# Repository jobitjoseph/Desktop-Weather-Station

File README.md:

# [Desktop-Weather-Station](https://circuitdigest.com/microcontroller-projects/)

---
<p>
  In today’s fast-paced world, many of us spend long hours indoors—whether working from home, studying, or just managing our daily routines. Natural cues like changing skies, outdoor temperatures, or the feel of humidity are often lost behind four walls and closed windows. This can make it difficult to stay aware of what’s happening outside, especially when our focus is tied to digital devices. Having a dedicated, always-visible weather display on your desk adds a subtle but meaningful connection to the outside world. It’s a small touch that can help with planning your day, knowing when to grab a jacket before stepping out, or simply enjoying the gentle reminder that time and weather continue to change beyond the screen.
</p>

<p>This project offers a practical way to build a clean and minimal weather station using an ESP32 microcontroller and an E-Ink display. The use of E-Ink ensures that the display remains readable even without constant power, making it a perfect fit for battery-powered desktop use. Once connected to Wi-Fi, the station fetches real-time weather data such as temperature, humidity, and current conditions using the OpenWeatherMap API. It also monitors indoor temperature and humidity with the help of a built-in sensor and adds to the data displayed on the screen. The device automatically updates itself at fixed intervals and enters deep sleep to conserve energy. Once assembled, it becomes a quiet and elegant companion on your desk—keeping you informed, without the distractions of a smartphone or computer screen.</p>

The firmware part of this project builds upon the excellent work of [David Bird](https://github.com/G6EJD/ESP32-e-Paper-Weather-Display). The code has been adapted from his original implementation.

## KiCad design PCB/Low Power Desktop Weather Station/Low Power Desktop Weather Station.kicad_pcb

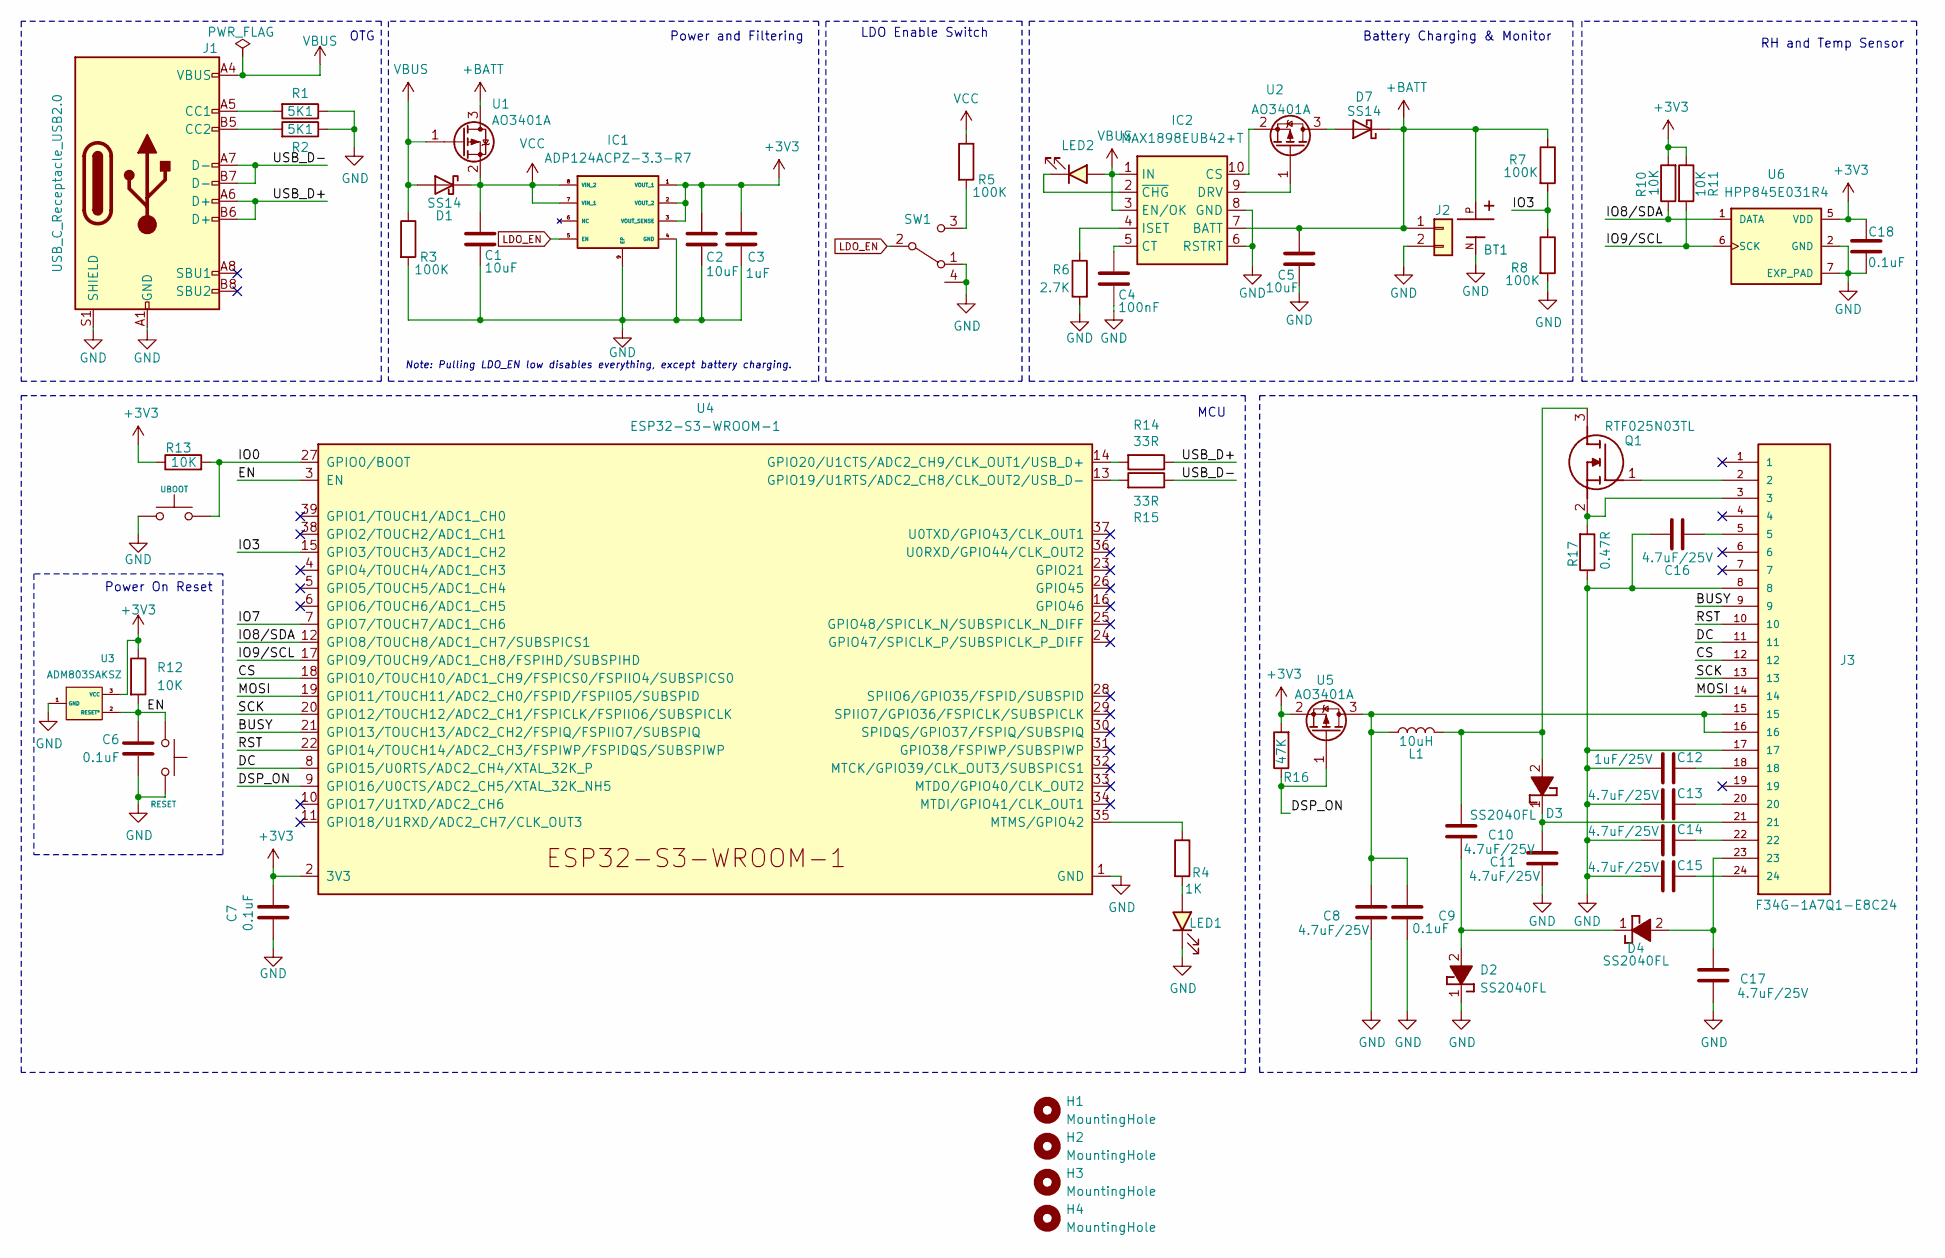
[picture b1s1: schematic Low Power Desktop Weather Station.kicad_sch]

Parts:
BOOT1: RESET; Tactile 3x4x2mm TS-A010; DigiKey Part Number 2449-CS1213AGF160CT-ND
BOOT2: UBOOT; Tactile 3x4x2mm TS-A010; DigiKey Part Number 2449-CS1213AGF160CT-ND
BT1: BU2450SM-JJ-G; BAT_BU2450SM-JJ-G; PARTREV J
C1: 10uF; C_0603_1608Metric; DigiKey Part Number 1276-1038-1-ND
C2, C5: 10uF; C_0603_1608Metric; DigiKey Part Number 490-10692-1-ND
C3: 1uF; C_0603_1608Metric; DigiKey Part Number 490-10018-1-ND
C4: 100nF; C_0603_1608Metric; DigiKey Part Number 490-10692-1-ND
C6, C7, C18: 0.1uF; C_0603_1608Metric; DigiKey Part Number 490-6328-1-ND
C8, C10, C11, C13, C14, C15, C16, C17: 4.7uF/25V; C_0603_1608Metric
C9: 0.1uF; C_0603_1608Metric
C12: 1uF/25V; C_0603_1608Metric
D1: SS14; D_SMA; DigiKey Part Number SS14-M3/5ATGICT-ND
D2, D3, D4: SS2040FL; SODFL3618X110N; Mouser Part Number 241-SS2040FLR100001
D7: SS14; D_SMA
H1, H2, H3, H4: MountingHole; MountingHole_2.5mm_Pad
IC1: ADP124ACPZ-3.3-R7; SON50P200X200X65-9N-D; Mouser Part Number 584-ADP124ACPZ-3.3R7
IC2: MAX1898EUB42+T; SOP50P490X110-10N; DigiKey Part Number MAX1898EUB42+TCT-ND
J1: USB_C_Receptacle_USB2.0; USB_C_Receptacle_XKB_U262-16XN-4BVC11; DigiKey Part Number 2073-USB4105-GF-ACT-ND
J2: B2B-PH-SM4-TB(LF)(SN); JST_PH_S2B-PH-SM4-TB_1x02-1MP_P2.00mm_Horizontal; DigiKey Part Number 455-1704-ND
J3: F34G-1A7Q1-E8C24; AMPHENOL_F34G-1A7Q1-E8C24; PARTREV A
L1: 10uH; L_Taiyo-Yuden_MD-4040
LED1: LED Red; LED_0603_1608Metric; DigiKey Part Number 3147-B1911USD-20D000114U1930CT-ND
LED2: LED Blue; LED_0603_1608Metric; DigiKey Part Number 3147-B1911NB--20C005314U1930CT-ND
Q1: RTF025N03TL; Mouser Part Number 755-RTF025N03TL
R1, R2: 5K1; R_0603_1608Metric; DigiKey Part Number P5.10KHCT-ND
R3, R5, R7, R8: 100K; R_0603_1608Metric; DigiKey Part Number P100KHCT-ND
R4: 1K; R_0603_1608Metric; DigiKey Part Number P1.00KHCT-ND
R6: 2.7K; R_0603_1608Metric; DigiKey Part Number P1.40KHCT-ND
R10, R11, R12, R13: 10K; R_0603_1608Metric; DigiKey Part Number P10.0KHCT-ND
R14, R15: 33R; R_0603_1608Metric; DigiKey Part Number P17467CT-ND
R16: 47K; R_0603_1608Metric; DigiKey Part Number P10.0KHCT-ND
R17: 0.47R; R_0805_2012Metric; DigiKey Part Number P17467CT-ND
SW1: SLW-66527511-SMT-TR; slide switch spdt; DigiKey Part Number 2223-SLW-66527511-SMT-TRCT-ND
U1, U2, U5: AO3401A; SOT-23; DigiKey Part Number AO3401-ND
U3: ADM803SAKSZ; KS_3_ADI; DigiKey Part Number 505-ADM803SAKSZ-REEL7CT-ND
U4: ESP32-S3-WROOM-1; DigiKey Part Number 1965-ESP32-S3-WROOM-1-N16R8CT-ND
U6: HPP845E031R4; SON100P300X300X90-7N; PARTREV 8

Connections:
+3V3: C2.1, C3.1, C7.1, C18.1, IC1.1 (VOUT_1), IC1.2 (VOUT_2), IC1.3 (VOUT_SENSE), R10.2, R11.1, R12.1, R13.1, R16.2, U3.3 (VCC), U4.2 (3V3), U5.2 (S), U6.5 (VDD)
+BATT: BT1.P, C5.1, D7.1 (K), IC2.7 (BATT), J2.1, R7.1, U1.3 (D)
/BUSY: J3.9, U4.21 (GPIO13/TOUCH13/ADC2_CH2/FSPIQ/FSPIIO7/S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)
/CS: J3.12, U4.18 (GPIO10/TOUCH10/ADC1_CH9/FSPICS0/FSPIIO4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)
/DC: J3.11, U4.8 (GPIO15/U0RTS/ADC2_CH4/XTAL_32K_P)
/DSP_ON: R16.1, U4.9 (GPIO16/U0CTS/ADC2_CH5/XTAL_32K_NH5), U5.1 (G)
/EN: BOOT1.1, C6.1, R12.2, U3.2 (RESET*), U4.3 (EN)
/IO0: BOOT2.1, R13.2, U4.27 (GPIO0/BOOT)
/IO3: R7.2, R8.1, U4.15 (GPIO3/TOUCH3/ADC1_CH2)
/IO7: U4.7 (GPIO7/TOUCH7/ADC1_CH6)
/IO8/SDA: R10.1, U4.12 (GPIO8/TOUCH8/ADC1_CH7/SUBSPICS1), U6.1 (DATA)
/IO9/SCL: R11.2, U4.17 (GPIO9/TOUCH9/ADC1_CH8/FSPIHD/SUBSPIHD), U6.6 (SCK)
/MOSI: J3.14, U4.19 (GPIO11/TOUCH11/ADC2_CH0/FSPID/FSPIIO5/S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)
/RST: J3.10, U4.22 (GPIO14/TOUCH14/ADC2_CH3/FSPIWP/FSPIDQS/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)
/SCK: J3.13, U4.20 (GPIO12/TOUCH12/ADC2_CH1/FSPICLK/FSPIIO6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)
/USB_D+: J1.A6 (D+), J1.B6 (D+), R14.1
/USB_D-: J1.A7 (D-), J1.B7 (D-), R15.1
GND: BOOT1.2, BOOT2.2, BT1.N, C1.2, C2.2, C3.2, C4.2, C5.2, C6.2, C7.2, C8.2, C9.2, C11.2, C12.1, C13.1, C14.1, C15.1, C16.1, C17.2, C18.2, D2.1 (K), IC1.4 (GND), IC1.9 (EP), IC2.6 (RSTRT), IC2.8 (GND), J1.A1 (GND), J1.A12 (GND), J1.B1 (GND), J1.B12 (GND), J1.S1 (SHIELD), J2.2, J3.8, J3.17, LED1.1 (K), R1.1, R2.1, R3.2, R6.2, R8.2, R17.1, SW1.1 (A), SW1.4, U3.1 (GND), U4.1 (GND), U4.40 (GND), U4.41 (GND), U6.2 (GND), U6.7 (EXP_PAD)
LDO_EN: IC1.5 (EN), SW1.2 (B)
unnamed: C12.2, J3.18
unnamed: C13.2, J3.20
unnamed: C14.2, J3.22
unnamed: C15.2, J3.24
unnamed: C16.2, J3.5
unnamed: C10.2, D2.2 (A), D4.1 (K)
unnamed: C10.1, D3.2 (A), L1.2, Q1.3 (D)
unnamed: C11.1, D3.1 (K), J3.21
unnamed: C17.1, D4.2 (A), J3.23
unnamed: D7.2 (A), U2.3 (D)
unnamed: IC2.10 (CS), U2.2 (S)
unnamed: C4.1, IC2.5 (CT)
unnamed: IC2.9 (DRV), U2.1 (G)
unnamed: IC2.4 (ISET), R6.1
unnamed: IC2.2 (~CHG), LED2.1 (K)
unnamed: J1.A5 (CC1), R1.2
unnamed: J1.B5 (CC2), R2.2
unnamed: LED1.2 (A), R4.2
unnamed: J3.2, Q1.1 (G)
unnamed: J3.3, Q1.2 (S), R17.2
unnamed: R5.2, SW1.3 (C)
unnamed: R15.2, U4.13 (GPIO19/U1RTS/ADC2_CH8/CLK_OUT2/USB_D-)
unnamed: R14.2, U4.14 (GPIO20/U1CTS/ADC2_CH9/CLK_OUT1/USB_D+)
unnamed: R4.1, U4.35 (MTMS/GPIO42)
unnamed: C8.1, C9.1, J3.15, J3.16, L1.1, U5.3 (D)
VBUS: D1.2 (A), IC2.1 (IN), IC2.3 (EN/OK), J1.A4 (VBUS), J1.A9 (VBUS), J1.B4 (VBUS), J1.B9 (VBUS), LED2.2 (A), R3.1, U1.1 (G)
VCC: C1.1, D1.1 (K), IC1.7 (VIN_1), IC1.8 (VIN_2), R5.1, U1.2 (S)

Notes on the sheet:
MCU
Note: Pulling LDO_EN low disables everything, except battery charging.
RH and Temp Sensor
OTG
Power On Reset
Battery Charging & Monitor
Power and Filtering
LDO Enable Switch

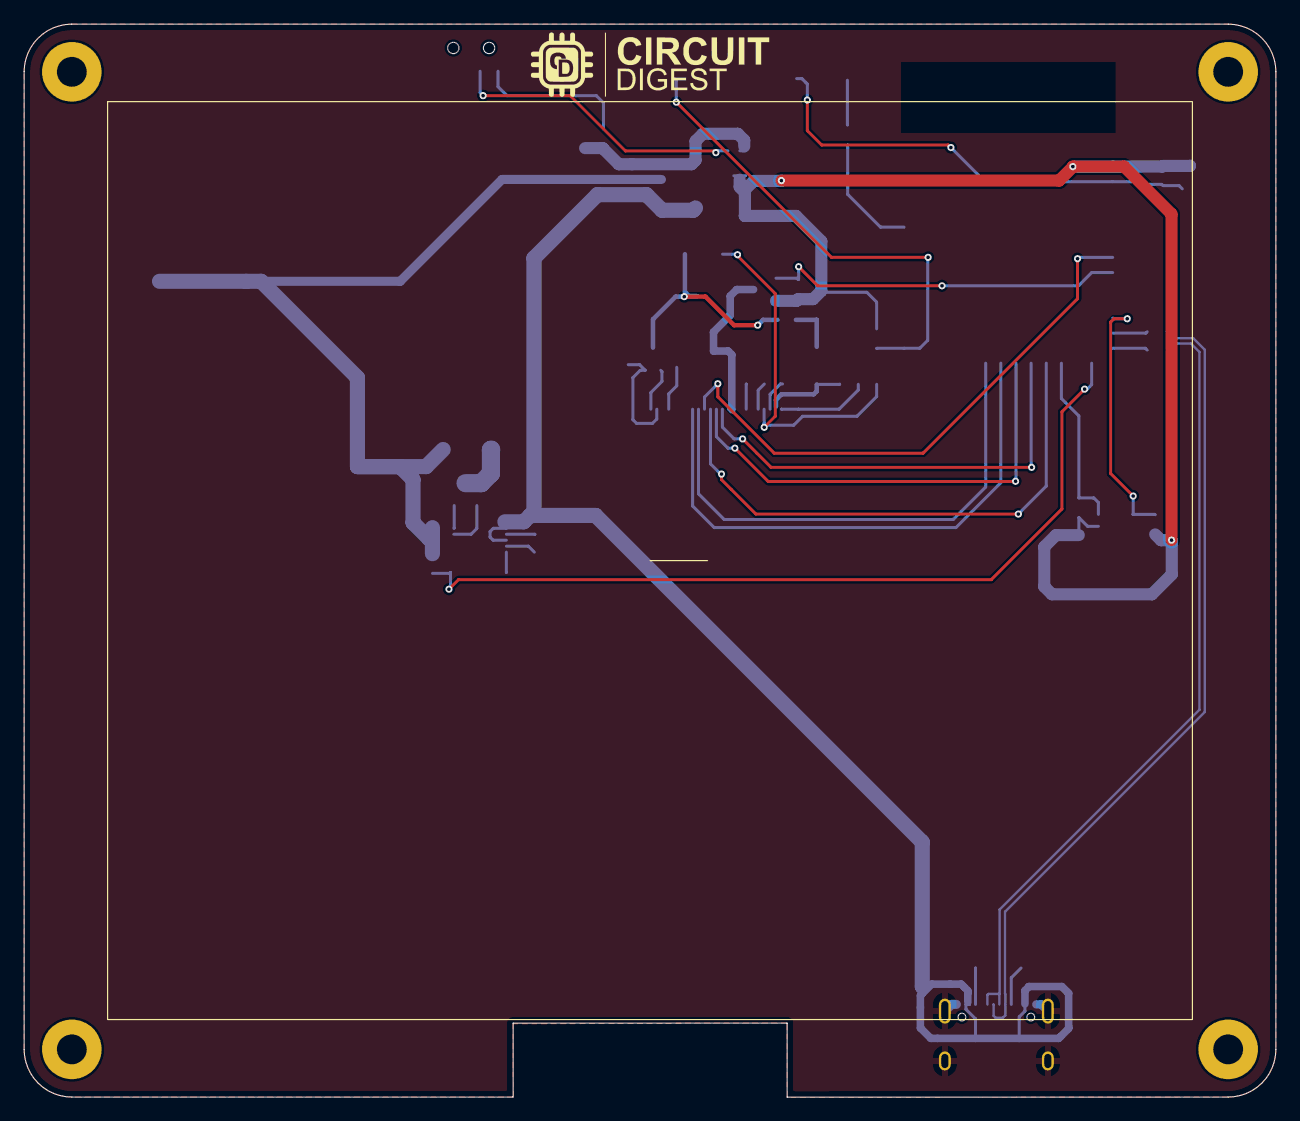
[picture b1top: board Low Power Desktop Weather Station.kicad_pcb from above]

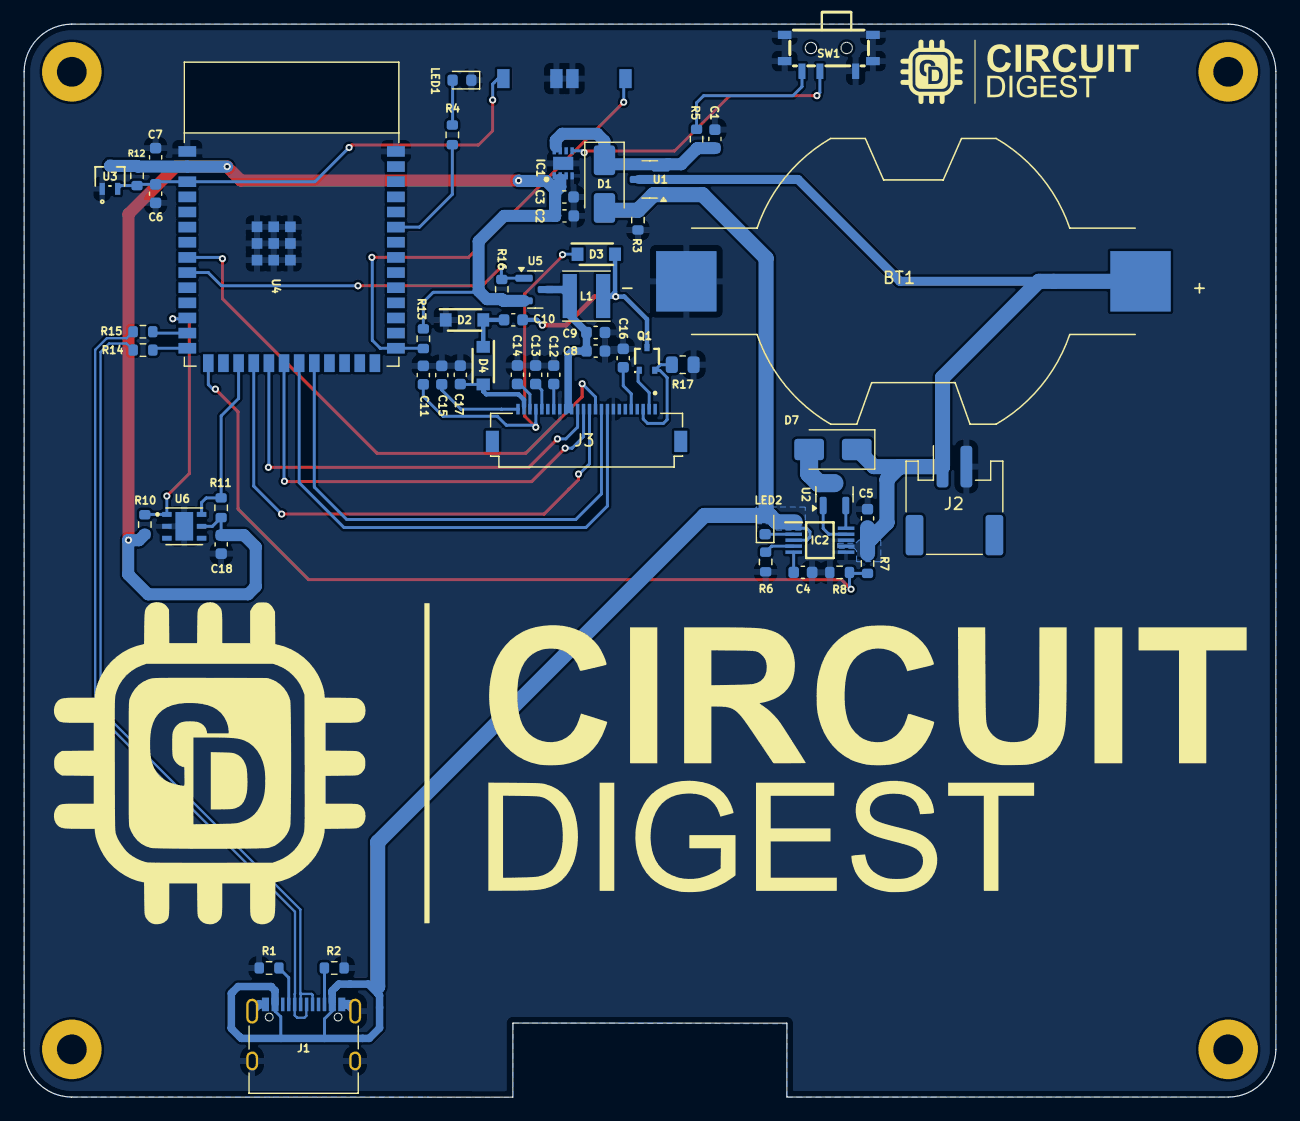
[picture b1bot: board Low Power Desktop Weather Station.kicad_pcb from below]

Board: 2 copper layers, 105.0 x 90.0 mm, 62 parts (57 on the bottom side), 45 nets.

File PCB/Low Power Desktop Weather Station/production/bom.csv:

Designator,Footprint,Quantity,Value,LCSC Part #
BOOT1,Tactile 3x4x2mm TS-A010,1,RESET,
BOOT2,Tactile 3x4x2mm TS-A010,1,UBOOT,
BT1,BAT_BU2450SM-JJ-G,1,BU2450SM-JJ-G,
"C1, C2, C5",0603,3,10uF,
"C10, C11, C13, C14, C15, C16, C17, C8",0603,8,4.7uF/25V,
C12,0603,1,1uF/25V,
"C18, C6, C7",0603,3,0.1uF,
C3,0603,1,1uF,
C4,0603,1,100nF,
C9,0603,1,0.1uF,
"D1, D7",D_SMA,2,SS14,
"D2, D3, D4",SODFL3618X110N,3,SS2040FL,
IC1,SON50P200X200X65-9N-D,1,ADP124ACPZ-3.3-R7,
IC2,SOP50P490X110-10N,1,MAX1898EUB42+T,
J1,USB_C_Receptacle_XKB_U262-16XN-4BVC11,1,USB_C_Receptacle_USB2.0,
J2,JST_PH_S2B-PH-SM4-TB_1x02-1MP_P2.00mm_Horizontal,1,B2B-PH-SM4-TB(LF)(SN),
J3,AMPHENOL_F34G-1A7Q1-E8C24,1,F34G-1A7Q1-E8C24,
L1,L_Taiyo-Yuden_MD-4040,1,10uH,
LED1,0603,1,LED Red,
LED2,0603,1,LED Blue,
Q1,RTF025N03TL,1,RTF025N03TL,
"R1, R2",0603,2,5K1,
"R10, R11, R12, R13",0603,4,10K,
"R14, R15",0603,2,33R,
R16,0603,1,47K,
R17,0805,1,0.47R,
"R3, R5, R7, R8",0603,4,100K,
R4,0603,1,1K,
R6,0603,1,2.7K,
SW1,slide switch spdt,1,SLW-66527511-SMT-TR,
"U1, U2, U5",SOT-23,3,AO3401A,
U3,KS_3_ADI,1,ADM803SAKSZ,
U4,ESP32-S3-WROOM-1,1,ESP32-S3-WROOM-1,
U6,SON100P300X300X90-7N,1,HPP845E031R4,
